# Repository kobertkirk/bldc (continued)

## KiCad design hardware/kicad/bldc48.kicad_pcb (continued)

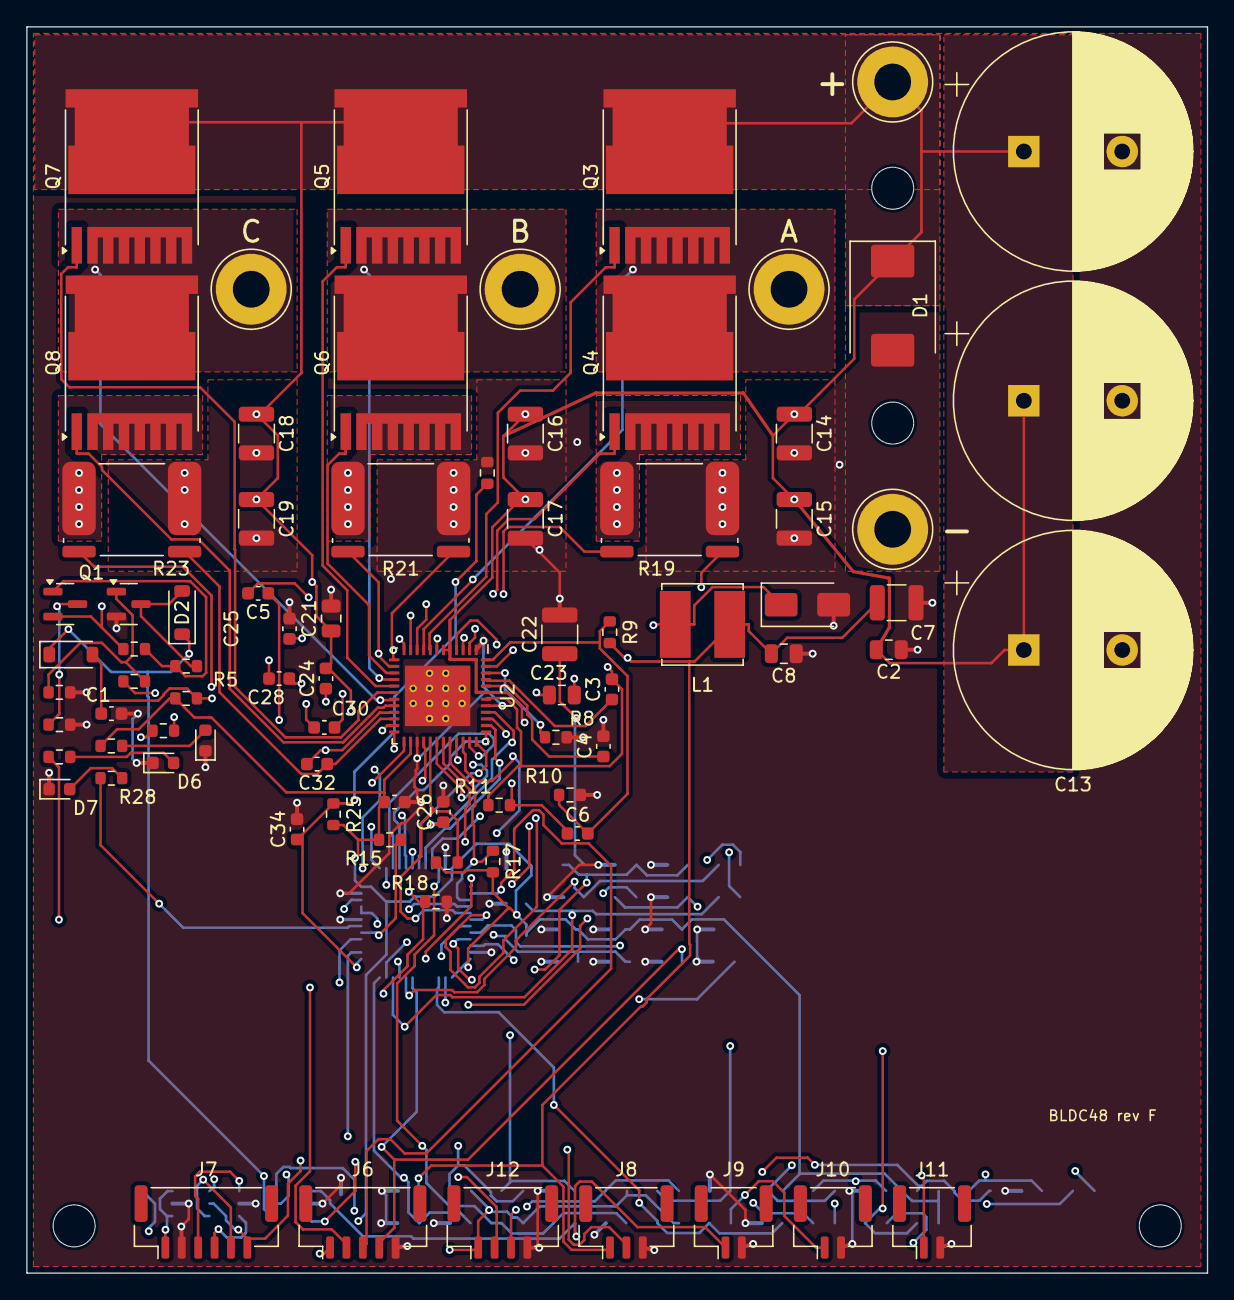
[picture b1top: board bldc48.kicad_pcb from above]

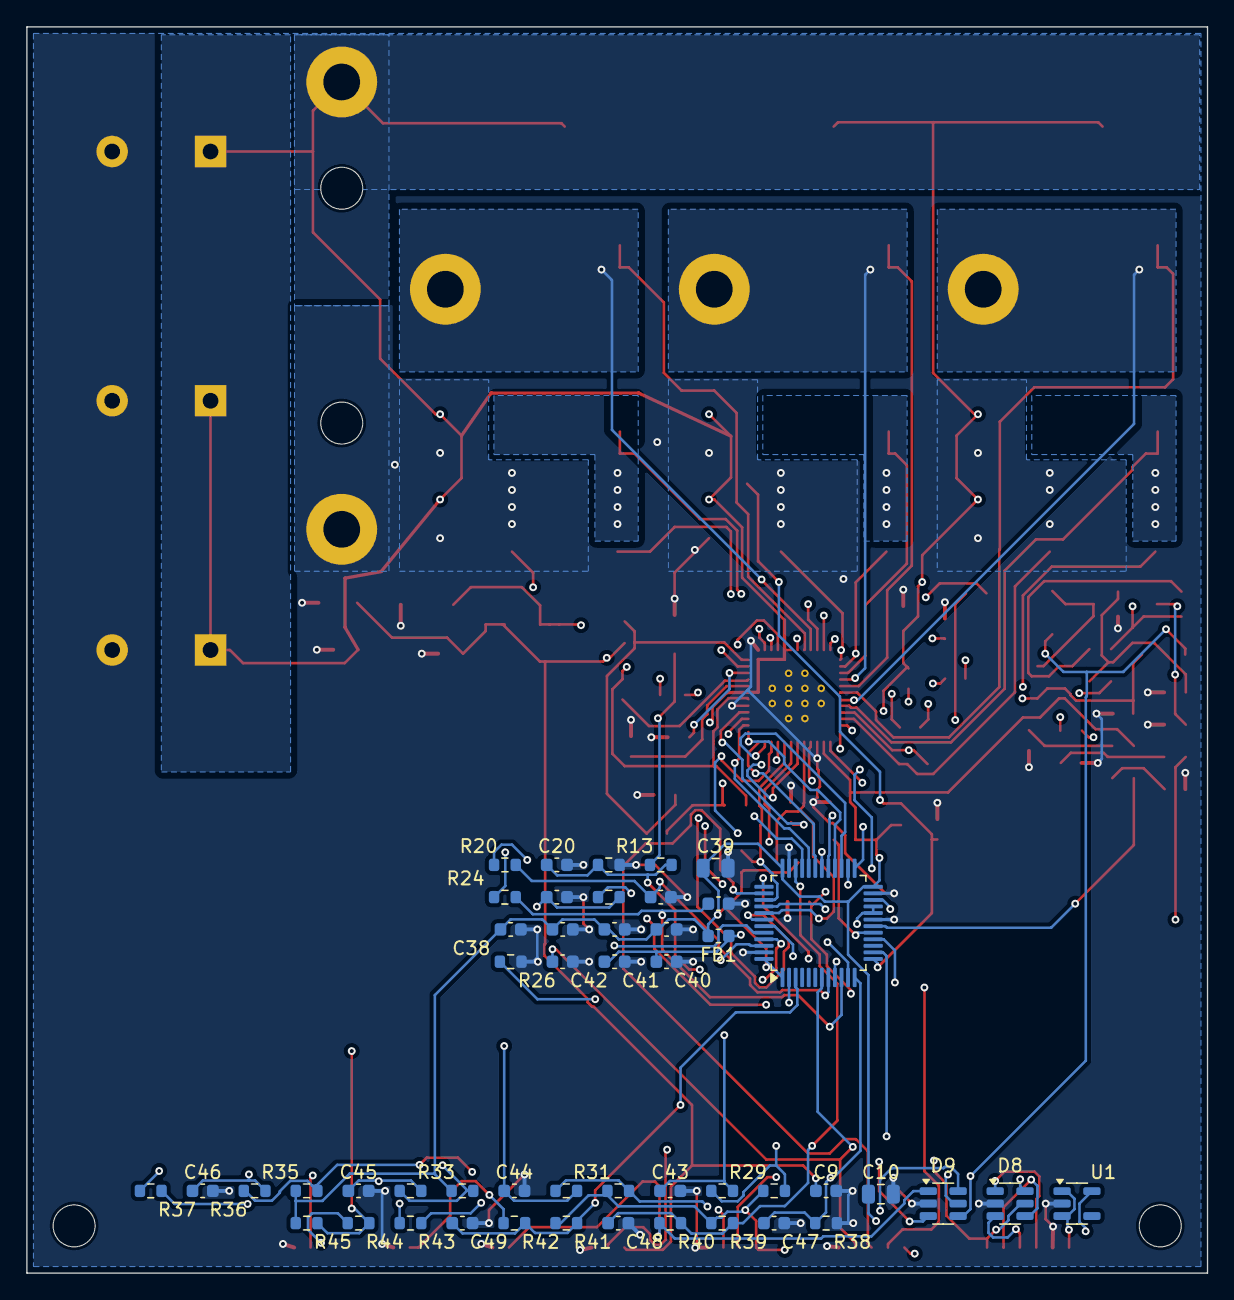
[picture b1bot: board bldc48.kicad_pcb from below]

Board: 4 copper layers, 90.0 x 95.0 mm, 133 parts (49 on the bottom side), 89 nets.

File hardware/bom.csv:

Qty,Value,Footprint,Part / notes,References
3,1000u/100V,CP_Radial_D18.0mm_P7.50mm,"Aishi ERS1KM102M35OT (LCSC C724666), 18x35 mm, 7.5 mm pitch, 105 C 10000 h",C11 C12 C13
12,100n,C_0603_1608Metric,,C27 C34 C35 C36 C37 C38 C41 C42 C46 C47 C48 C49
1,100n/100V,C_0805_2012Metric,X7R 0805 100V,C21
3,10n,C_0603_1608Metric,,C1 C3 C20
9,1n,C_0603_1608Metric,,C28 C29 C30 C31 C32 C33 C43 C44 C45
4,1u,C_0603_1608Metric,,C4 C9 C26 C40
1,1u/100V,C_0805_2012Metric,,C2
2,1u/16V,C_0603_1608Metric,,C24 C25
7,2.2u/100V,C_1210_3225Metric,X7R 1210 100V (e.g. GRM32ER72A225KA35),C14 C15 C16 C17 C18 C19 C22
1,22u/10V,C_1210_3225Metric,X5R/X7R 1210 10V,C7
1,330p,C_0603_1608Metric,,C6
3,4.7u,C_0805_2012Metric,,C8 C10 C39
1,47n,C_0603_1608Metric,,C5
1,47n/100V,C_0805_2012Metric,,C23
1,1N4148W,D_SOD-123,100V signal diode SOD-123,D2
1,BAT46W,D_SOD-123,100V Schottky SOD-123,D3
2,ESDA6V1-5SC6,SOT-23-6,ST ESDA6V1-5SC6 (LCSC C6650),D8 D9
2,GREEN,LED_0603_1608Metric,,D5 D6
1,RED,LED_0603_1608Metric,,D7
1,SMCJ60CA,D_SMC,"TVS 60V standoff, 1500W, SMC (Littelfuse, LCSC C151290)",D1
1,SS110,D_SMA,"100 V 1 A Schottky, SMA (e.g. MDD SS110)",D4
1,600R@100MHz,L_0603_1608Metric,,FB1
4,M3,MountingHole_3.2mm_M3,,H1 H2 H3 H4
1,BAT+,SolderWire_12AWG_D2.8mm_OD5.4mm,"12 AWG wire, soldered",J1
1,BAT-,SolderWire_12AWG_D2.8mm_OD5.4mm,"12 AWG wire, soldered",J2
1,BRAKE,JST_GH_BM02B-GHS-TBT_1x02-1MP_P1.25mm_Vertical,"JST BM02B-GHS-TBT (1.25 mm, latching)",J10
1,FWD/REV,JST_GH_BM02B-GHS-TBT_1x02-1MP_P1.25mm_Vertical,"JST BM02B-GHS-TBT (1.25 mm, latching)",J9
1,HALL,JST_GH_BM06B-GHS-TBT_1x06-1MP_P1.25mm_Vertical,"JST BM06B-GHS-TBT (1.25 mm, latching)",J7
1,MOTOR_A,SolderWire_12AWG_D2.8mm_OD5.4mm,"12 AWG wire, soldered",J3
1,MOTOR_B,SolderWire_12AWG_D2.8mm_OD5.4mm,"12 AWG wire, soldered",J4
1,MOTOR_C,SolderWire_12AWG_D2.8mm_OD5.4mm,"12 AWG wire, soldered",J5
1,POWER_BTN,JST_GH_BM02B-GHS-TBT_1x02-1MP_P1.25mm_Vertical,"JST BM02B-GHS-TBT (1.25 mm, latching)",J11
1,SWD,JST_GH_BM05B-GHS-TBT_1x05-1MP_P1.25mm_Vertical,"JST BM05B-GHS-TBT (1.25 mm, latching)",J6
1,THROTTLE,JST_GH_BM03B-GHS-TBT_1x03-1MP_P1.25mm_Vertical,"JST BM03B-GHS-TBT (1.25 mm, latching)",J8
1,UART,JST_GH_BM04B-GHS-TBT_1x04-1MP_P1.25mm_Vertical,"JST BM04B-GHS-TBT (1.25 mm, latching)",J12
1,100u,L_Bourns_SRN6045TA,"Bourns SRN6045TA-101M or eq. (100 uH, Isat >= 0.5 A, 6x6 mm)",L1
6,IPT015N10N5,Infineon_PG-HSOF-8-1,Infineon IPT015N10N5ATMA1 (LCSC C108964),Q3 Q4 Q5 Q6 Q7 Q8
1,MMBTA42,SOT-23,,Q2
1,MMBTA92,SOT-23,,Q1
3,0.5m,R_Shunt_Isabellenhuette_BVR4026,"Bourns CSS4J-4026R-L500F (LCSC C2076423), 0.5 mOhm 1% 5 W",R19 R21 R23
5,100R,R_0603_1608Metric,,R20 R22 R24 R43 R44
6,100k,R_0603_1608Metric,,R1 R4 R6 R8 R13 R18
10,10k,R_0603_1608Metric,,R3 R5 R15 R17 R25 R26 R35 R39 R41 R45
1,12k,R_0603_1608Metric,,R37
1,150k,R_0603_1608Metric,,R7
8,1k,R_0603_1608Metric,,R27 R28 R30 R32 R34 R36 R40 R42
4,2.2k,R_0603_1608Metric,,R12 R29 R31 R33
1,22k,R_0603_1608Metric,,R38
2,4.02k,R_0603_1608Metric,,R9 R10
1,4.7k,R_0603_1608Metric,,R16
1,47k,R_0603_1608Metric,,R2
1,5.6k,R_0603_1608Metric,,R14
1,8.2k,R_0603_1608Metric,,R11
1,10k B3435,R_0603_1608Metric,Murata NCP18XH103F03RB (LCSC C13564),TH1
1,AP2112K-3.3,SOT-23-5,Diodes AP2112K-3.3TRG1 (LCSC C51118),U1
1,DRV8353RS,TI-RGZ-48-QFN,TI DRV8353RSRGZR (LCSC C506246),U2
1,STM32G431CBT6,LQFP-48_7x7mm_P0.5mm,ST STM32G431CBT6 (LCSC C529355),U3

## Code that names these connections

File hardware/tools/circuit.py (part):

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# --- Soft power latch ---------------------------------------------------------
# Momentary switch pulls PWR_SW to GND (switch only ever sees <3.3 V) -> current
# flows out of Q1 base through R(47k) + D -> Q1 (high-voltage PNP) turns on ->
# EN_RAW feeds the DRV8353 buck's RT/SD pin, which shuts the buck down when it
# is pulled low -> 5 V and 3.3 V come up -> MCU boots and drives PWR_HOLD high
# (Q2 keeps Q1 on).  To switch off the MCU sees a long press on PWR_BTN, waits
# for release, drops PWR_HOLD.
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part(S, 'U', 'MCU_ST_STM32G4:STM32G431CBTx', 'STM32G431CBT6', 'Package_QFP:LQFP-48_7x7mm_P0.5mm', {
    'VBAT': '+3V3', 'VDD': '+3V3', '24': '+3V3', '36': '+3V3', '48': '+3V3',
    'VDDA': '+3V3A', 'VREF+': '+3V3A', 'VSSA': 'GND', 'VSS': 'GND', '23': 'GND',
    'PG10': 'NRST',
    # TIM1 complementary PWM
    'PA8': 'PWM_AH', 'PA9': 'PWM_BH', 'PA10': 'PWM_CH',
    'PB13': 'PWM_AL', 'PB14': 'PWM_BL', 'PB15': 'PWM_CL',
    # ADC
    'PA0': 'ISENSE_A', 'PA1': 'ISENSE_B', 'PA2': 'ISENSE_C', 'PA3': 'VBUS_SENSE',
    'PA4': 'THROTTLE', 'PA5': 'TEMP_FET', 'PA6': 'TEMP_MOTOR',
    # Halls (EXTI10..12)
    'PB10': 'HALL_A', 'PB11': 'HALL_B', 'PB12': 'HALL_C',
    # UART (USART1)
    'PB6': 'UART_TX', 'PB7': 'UART_RX',
    # DRV8353RS: SPI1 (AF5) + enable / fault
    'PB3': 'DRV_SCK', 'PB4': 'DRV_SDO', 'PB5': 'DRV_SDI', 'PA15': 'DRV_CS',
    'PB0': 'DRV_EN', 'PB1': 'DRV_FAULT',
    # switches / power
    'PA11': 'PWR_BTN', 'PA12': 'DIR_SW', 'PC14': 'BRAKE', 'PB9': 'PWR_HOLD',
    'PB8': 'BOOT0', 'PC13': 'LED_STATUS', 'PB2': 'LED_FAULT',
    # SWD
    'PA13': 'SWDIO', 'PA14': 'SWCLK',
    # unused
    'PA7': None, 'PC15': None, 'PF0': None, 'PF1': None,
})
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
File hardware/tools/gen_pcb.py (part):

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                return f'shunt{ph}'
            if ref.startswith('J') and f'SW_{ph}' in pins:
                return f'term{ph}'
        if pins & {'VBUS_SENSE', 'ISENSE_A', 'ISENSE_B', 'ISENSE_C'}:
            return 'mcu'                      # ADC-side filters / divider next to the MCU
        return 'drv'                          # DRV passives
    if s == 'power':
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            return 'batterm'
        if v == 'SMCJ60CA':
            return 'tvs'
        if pins & {'BST5', 'FB5', 'RIP5', 'RT_SD', 'RCL', 'VCC_B'} and lib != 'Device:L' \
                and 'EN_RAW' not in pins:
            return 'drv'                      # tied to DRV8353 buck pins: keep them at the pins
        if pins & {'SW5'} or (v == '1u/100V') or \
                (pins <= {'+5V', 'GND'} and lib != 'Device:LED' and v != '1u'):
            return 'buck'
        if any(n in pins for n in ('LATCH_B', 'LATCH_PULL', 'HOLD_B', 'PWR_BTN', 'EN_RAW')):
            return 'latch'
        if lib == 'Device:LED' or 'PWR_LED_A' in pins:
            return 'leds'
        return 'io'                           # LDO: bottom side with the I/O parts
    if s == 'mcu':
        if ref.startswith('J'):
            return 'conn'
        if lib == 'Device:LED' or pins & {'LED_STATUS_A', 'LED_FAULT_A'}:
            return 'leds'
        return 'mcu'
    if s == 'io':
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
